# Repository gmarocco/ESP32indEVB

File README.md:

# ESP32indEVB
ESP32-S3 industrial development board

This board is based on ESP32-S3 chip and microcontoller
 - There are the following physical communication interfaces
   
 a) debug USB (it is connected to a UARTport of ESP32-S3)  
 
 b) native USB 
 
 c) isolated CANBUS with termination resistor 
 
 d) isolated RS485 with termination resistor 
 
 - There is a 9 RGB LED matrix (WS2812B) 
 
- There are 9 ESD protected GPIOs 

 - There is a free section of testpoints for experiment 

This is the third version of the board. With respect to the second version, some nets have been renamed and stiching vias along the board perimeter have been added

  You can open and modify the project with KiCad 9 release 
  For questions, feedback or proposals you can contact me at the following email: info@pcbsemplice.com
  
 !!! It is not allowed to reproduce the board for mass production and for business purposes. If you have a business proposal you can write at the following email: info@pcbsemplice.com
 
  Are you interested in these projects and want to contribute to the development of boards and projects (including open-source), prototypes, and documentation? You can make a no-obligation donation at this PayPal link: https://shorturl.at/0LquK Every contribution, no matter how small, makes a difference. Thank you!

Scheda di sviluppo industriale ESP32-S3  
Questa scheda è basata sul chip e microcontrollore ESP32-S3 

- Sono presenti le seguenti interfacce di comunicazione fisica:
  
a) USB di debug (collegata a una porta UART dell'ESP32-S3)  

b) USB nativa 

c) CANBUS isolato con resistenza di terminazione 

d) RS485 isolata con resistenza di terminazione 

- È presente una matrice di 9 LED RGB (WS2812B)

- Sono presenti 9 GPIO con protezione ESD  

- È disponibile una sezione gratuita di testpoint per esperimenti  
È possibile aprire e modificare il progetto con KiCad versione 9  

Questa è la terza verione della scheda. Rispetto alla seconda versione sono state rinominate alcune net e sono stati aggiunti dei fori di via stiching lungo il perimetro della scheda

Per domande feedback e suggerimenti mi puoi contattare al seguente indirizzo email: info@pcbsemplice.com

!!! E' vietato riprodurre la scheda per scopi commerciali. Per proposte commerciali puoi scrivere a info@pcbsemplice.com

Se parli Italiano e stai inziando con KiCad ti segnalo il percorso KiCadSemplice (www.pcbsemplice.com/kicad)
Se sei interessato a progettare circuiti professionali , è disponibile un percorso personalizzato chiamato pcb-pro-accademy 
  -  
  -  
  -  

Ti interessano questi progetti e vuoi contribuire per lo sviluppo di schede e progetti (anche open-source), prototipi, documentazione ? Puoi effettuare una donazione senza impegno a questo link di Paypal https://shorturl.at/0LquK Ogni contributo, anche piccolo, fa la differenza. Grazie!

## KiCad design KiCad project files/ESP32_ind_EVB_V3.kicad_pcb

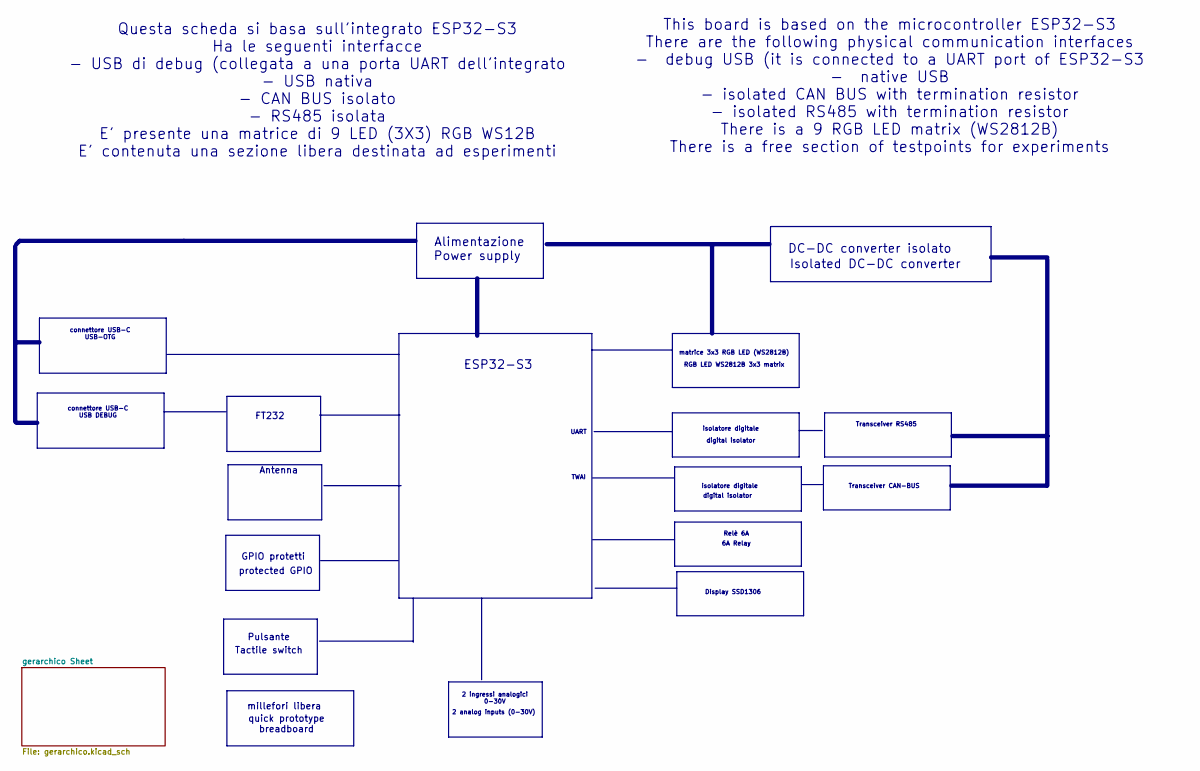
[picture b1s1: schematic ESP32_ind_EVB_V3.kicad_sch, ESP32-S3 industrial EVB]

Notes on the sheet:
TWAI
FT232
isolatore digitale
Transceiver RS485
matrice 3x3 RGB LED (WS2812B)
This board is based on the microcontroller ESP32-S3 There are the following physical communication interfaces - debug USB (it is connected to a UART port of ESP32-S3 - native USB - isolated CAN BUS with termination resistor - isolated RS485 with termination resistor There is a 9 RGB LED matrix (WS2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
Alimentazione
GPIO protetti
ESP32-S3
Transceiver CAN-BUS
millefori libera
Power supply
quick prototype breadboard
Questa scheda si basa sull'integrato ESP32-S3 Ha le seguenti interfacce - USB di debug (collegata a una porta UART dell'integrato - USB nativa - CAN BUS isolato - RS485 isolata E' presente una matrice di 9 LED (3X3) RGB WS12B E' contenuta una sezione libera destinata ad esperimenti
6A Relay
digital isolator
Pulsante
connettore USB-C USB-OTG
DC-DC converter isolato
Display SSD1306
Isolated DC-DC converter
2 analog inputs (0-30V)
protected GPIO
RGB LED WS2812B 3x3 matrix
Antenna
Relè 6A
2 ingressi analogici 0-30V
connettore USB-C USB DEBUG
Tactile switch
UART

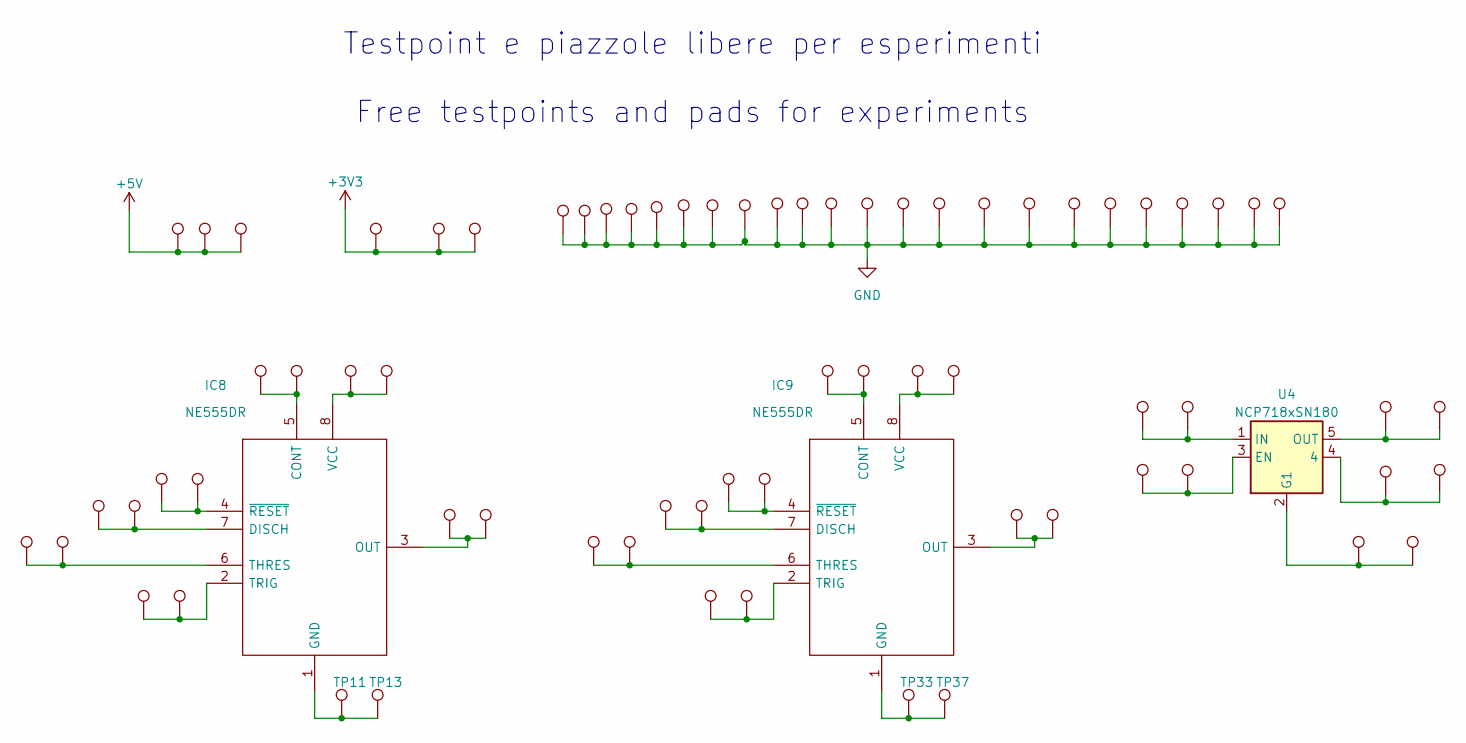
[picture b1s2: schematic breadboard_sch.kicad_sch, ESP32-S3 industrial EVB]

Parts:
IC8: NE555DR; SO-8_3.9x4.9mm_P1.27mm; Manufacturer_Part_Number NE555DR; Mouser Part Number 595-NE555DR
IC9: NE555DR; MSOP-8_3x3mm_P0.65mm; Manufacturer_Part_Number NE555DR; Mouser Part Number 595-NE555DR
TP1, TP2, TP3, TP4, TP5, TP6, TP7, TP8, TP9, TP10, TP11, TP12, TP13, TP14, TP15, TP16, TP17, TP18, TP19, TP20, TP21, TP22, TP23, TP24, TP25, TP26, TP27, TP28, TP29, TP30, TP31, TP32, TP33, TP34, TP35, TP36, TP37, TP38, TP39, TP40, TP41, TP42, TP43, TP44, TP45, TP46, TP47, TP48, TP49, TP50, TP51, TP52, TP53, TP54, TP55, TP56, TP57, TP58, TP59, TP60, TP61, TP62, TP63, TP64, TP65, TP66, TP67, TP68, TP69, TP70, TP71: TestPoint; TestPoint_Pad_through hole 1.5mm
U4: NCP718xSN180; SOT-23-5

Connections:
+3V3: TP25.1, TP29.1, TP30.1; also elsewhere on the board
+5V: TP17.1, TP18.1, TP19.1; also elsewhere on the board
GND: TP34.1, TP36.1, TP38.1, TP40.1, TP41.1, TP43.1, TP45.1, TP46.1, TP47.1, TP50.1, TP51.1, TP54.1, TP55.1, TP56.1, TP57.1, TP59.1, TP63.1, TP66.1, TP67.1, TP68.1, TP69.1, TP70.1, TP71.1; also elsewhere on the board
unnamed: IC8.5 (CONT), TP9.1, TP10.1
unnamed: IC8.7 (DISCH), TP3.1, TP4.1
unnamed: IC8.1 (GND), TP11.1, TP13.1
unnamed: IC8.3 (OUT), TP15.1, TP16.1
unnamed: IC8.6 (THRES), TP1.1, TP2.1
unnamed: IC8.2 (TRIG), TP5.1, TP7.1
unnamed: IC8.8 (VCC), TP12.1, TP14.1
unnamed: IC8.4 (~RESET), TP6.1, TP8.1
unnamed: IC9.5 (CONT), TP31.1, TP32.1
unnamed: IC9.7 (DISCH), TP22.1, TP23.1
unnamed: IC9.1 (GND), TP33.1, TP37.1
unnamed: IC9.3 (OUT), TP42.1, TP44.1
unnamed: IC9.6 (THRES), TP20.1, TP21.1
unnamed: IC9.2 (TRIG), TP24.1, TP27.1
unnamed: IC9.8 (VCC), TP35.1, TP39.1
unnamed: IC9.4 (~RESET), TP26.1, TP28.1
unnamed: TP61.1, TP65.1, U4.4
unnamed: TP49.1, TP53.1, U4.3 (EN)
unnamed: TP58.1, TP62.1, U4.2 (G1)
unnamed: TP48.1, TP52.1, U4.1 (IN)
unnamed: TP60.1, TP64.1, U4.5 (OUT)

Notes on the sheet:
Testpoint e piazzole libere per esperimenti Free testpoints and pads for experiments

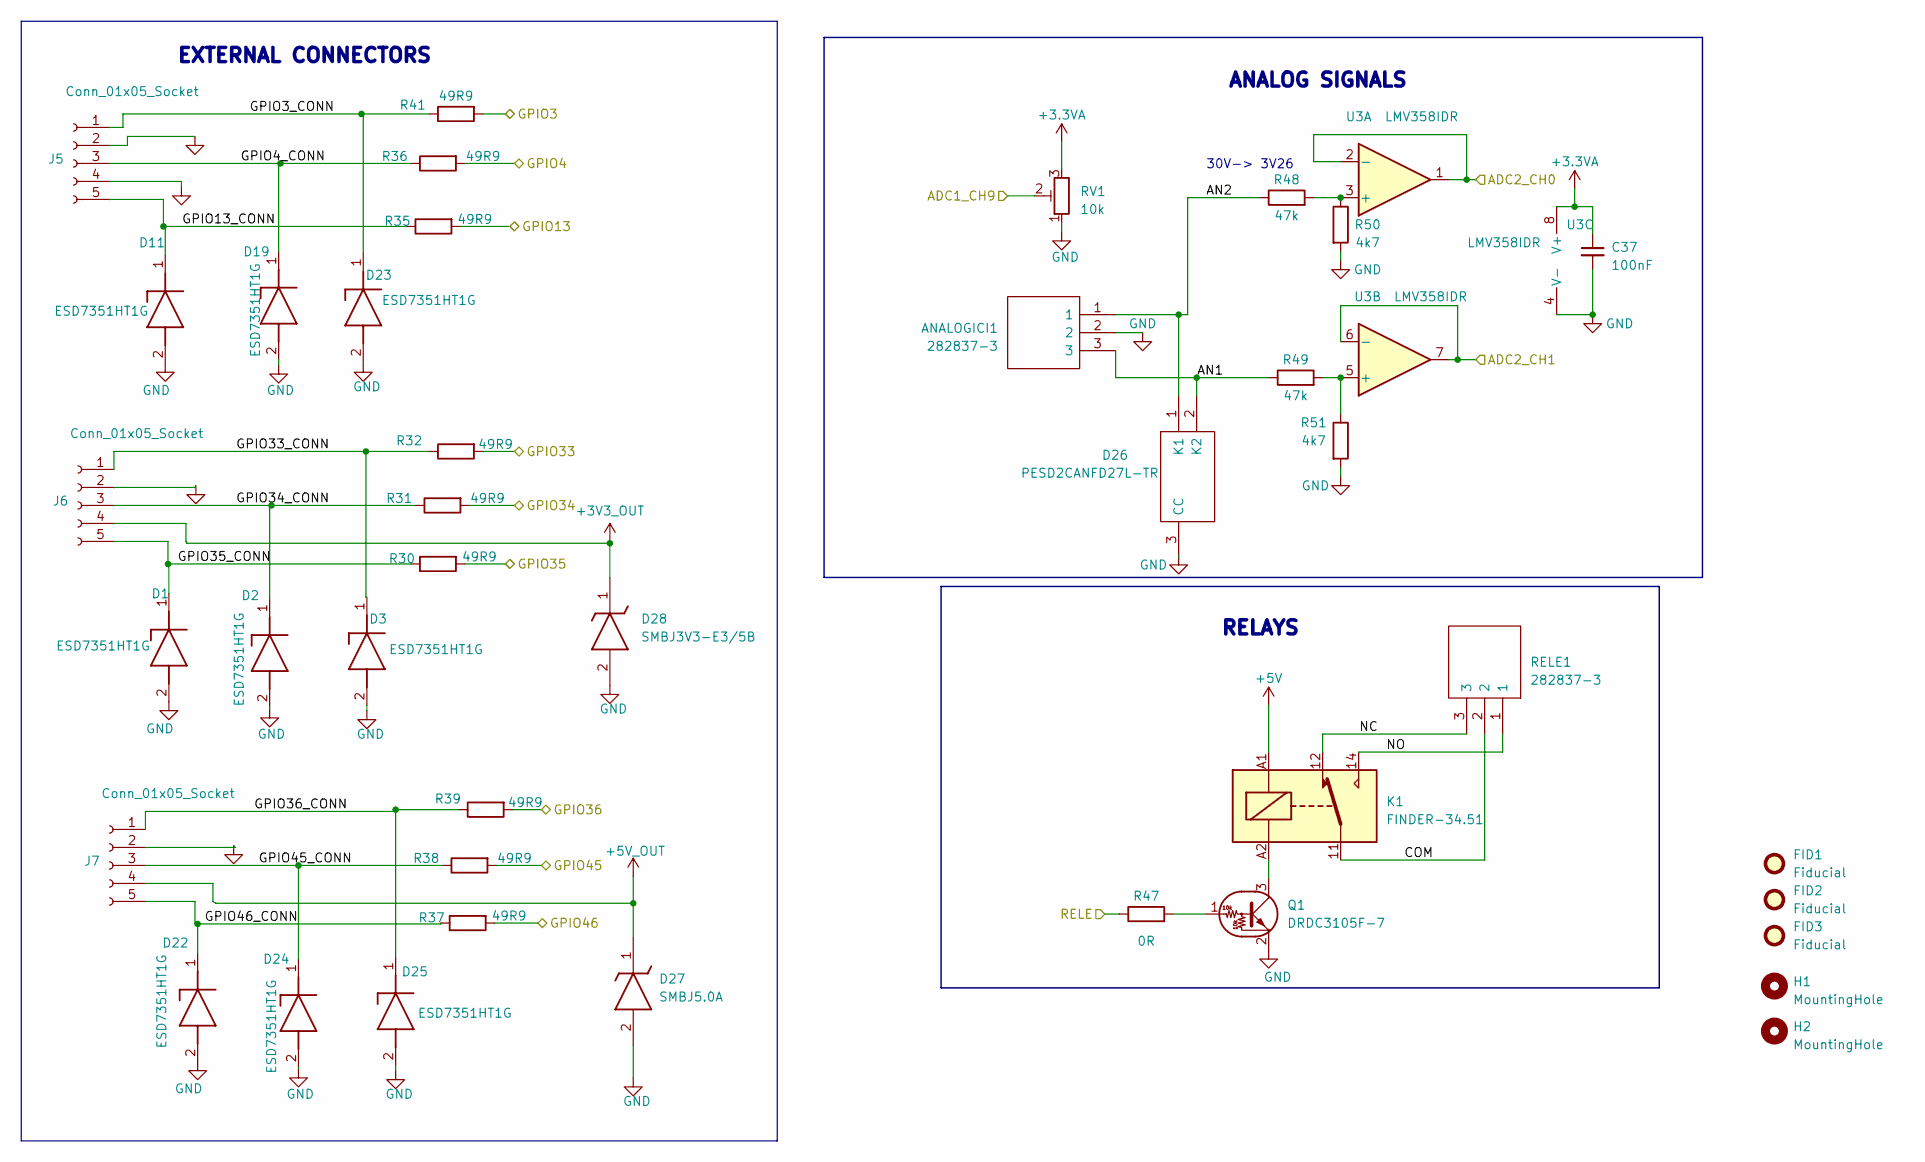
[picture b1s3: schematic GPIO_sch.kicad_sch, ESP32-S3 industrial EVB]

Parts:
ANALOGICI1: 282837-3; TerminalBlock_bornier-3_P5.08mm; Mouser Part Number 490-TB006-508-03BE
C37: 100nF; C_0603_1608Metric_Pad1.08x0.95mm_HandSolder
D1, D2, D3, D11, D19, D22, D23, D24, D25: ESD7351HT1G; SOD-323; Mouser Part Number 771-PESD3V3U1UB-T/R
D26: PESD2CANFD27L-TR; SOT-23-3; Mouser Part Number 771-PESD2CANFD24L-UX
D27: SMBJ5.0A; DIOM5436X244N; Mouser Part Number 78-SMBJ5.0A
D28: SMBJ3V3-E3/5B; DIOM5436X244N; Mouser Part Number 78-SMBJ5.0A
FID1, FID2, FID3: Fiducial; Fiducial_1.5mm_Mask3mm
H1, H2: MountingHole; MountingHole_3.2mm_M3
J5, J6, J7: Conn_01x05_Socket; PinSocket_1x05_P2.54mm_Vertical
K1: FINDER-34.51; Relay_SPDT_Finder_34.51_Vertical
Q1: DRDC3105F-7; SOT-23-3
R30, R31, R32, R35, R36, R37, R38, R39, R41: 49R9; R_0805_2012Metric_Pad1.20x1.40mm_HandSolder
R47: 0R; R_0603_1608Metric_Pad0.98x0.95mm_HandSolder
R48, R49: 47k; R_0603_1608Metric_Pad0.98x0.95mm_HandSolder
R50, R51: 4k7; R_0603_1608Metric_Pad0.98x0.95mm_HandSolder
RELE1: 282837-3; TerminalBlock_bornier-3_P5.08mm; Mouser Part Number 490-TB006-508-03BE
RV1: 10k; Potentiometer_Bourns_3314G_Vertical
U3: LMV358IDR; SO-8_3.9x4.9mm_P1.27mm

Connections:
+3.3VA: C37.1, RV1.3, U3.8 (V+); also elsewhere on the board
+3V3_OUT: D28.1 (K), J6.4; also elsewhere on the board
+5V: K1.A1; also elsewhere on the board
+5V_OUT: D27.1 (K), J7.4; also elsewhere on the board
/gerarchico Sheet/ESP32-S3 MCU/ADC1_CH9: RV1.2; also elsewhere on the board
/gerarchico Sheet/ESP32-S3 MCU/ADC2_CH0: U3.1, U3.2 (-); also elsewhere on the board
/gerarchico Sheet/ESP32-S3 MCU/ADC2_CH1: U3.6 (-), U3.7; also elsewhere on the board
/gerarchico Sheet/ESP32-S3 MCU/GPIO3: R41.2; also elsewhere on the board
/gerarchico Sheet/ESP32-S3 MCU/GPIO4: R36.2; also elsewhere on the board
/gerarchico Sheet/ESP32-S3 MCU/GPIO13: R35.2; also elsewhere on the board
/gerarchico Sheet/ESP32-S3 MCU/GPIO33: R32.2; also elsewhere on the board
/gerarchico Sheet/ESP32-S3 MCU/GPIO34: R31.2; also elsewhere on the board
/gerarchico Sheet/ESP32-S3 MCU/GPIO35: R30.2; also elsewhere on the board
/gerarchico Sheet/ESP32-S3 MCU/GPIO36: R39.2; also elsewhere on the board
/gerarchico Sheet/ESP32-S3 MCU/GPIO45: R38.2; also elsewhere on the board
/gerarchico Sheet/ESP32-S3 MCU/GPIO46: R37.2; also elsewhere on the board
/gerarchico Sheet/ESP32-S3 MCU/RELE: R47.1; also elsewhere on the board
/gerarchico Sheet/GPIO/AN1: ANALOGICI1.3, D26.2 (K2), R49.1
/gerarchico Sheet/GPIO/AN2: ANALOGICI1.1, D26.1 (K1), R48.1
/gerarchico Sheet/GPIO/COM: K1.11, RELE1.2
/gerarchico Sheet/GPIO/GPIO3_CONN: D23.1 (K), J5.1, R41.1
/gerarchico Sheet/GPIO/GPIO4_CONN: D19.1 (K), J5.3, R36.1
/gerarchico Sheet/GPIO/GPIO13_CONN: D11.1 (K), J5.5, R35.1
/gerarchico Sheet/GPIO/GPIO33_CONN: D3.1 (K), J6.1, R32.1
/gerarchico Sheet/GPIO/GPIO34_CONN: D2.1 (K), J6.3, R31.1
/gerarchico Sheet/GPIO/GPIO35_CONN: D1.1 (K), J6.5, R30.1
/gerarchico Sheet/GPIO/GPIO36_CONN: D25.1 (K), J7.1, R39.1
/gerarchico Sheet/GPIO/GPIO45_CONN: D24.1 (K), J7.3, R38.1
/gerarchico Sheet/GPIO/GPIO46_CONN: D22.1 (K), J7.5, R37.1
/gerarchico Sheet/GPIO/NC: K1.12, RELE1.3
/gerarchico Sheet/GPIO/NO: K1.14, RELE1.1
GND: ANALOGICI1.2, C37.2, D1.2 (A), D2.2 (A), D3.2 (A), D11.2 (A), D19.2 (A), D22.2 (A), D23.2 (A), D24.2 (A), D25.2 (A), D26.3 (CC), D27.2 (A), D28.2 (A), J5.2, J5.4, J6.2, J7.2, Q1.2 (E), R50.2, R51.2, RV1.1, U3.4 (V-); also elsewhere on the board
unnamed: Q1.1 (B), R47.2
unnamed: K1.A2, Q1.3 (C)
unnamed: R48.2, R50.1, U3.3 (+)
unnamed: R49.2, R51.1, U3.5 (+)

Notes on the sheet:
30V-> 3V26
ANALOG SIGNALS
RELAYS
EXTERNAL CONNECTORS

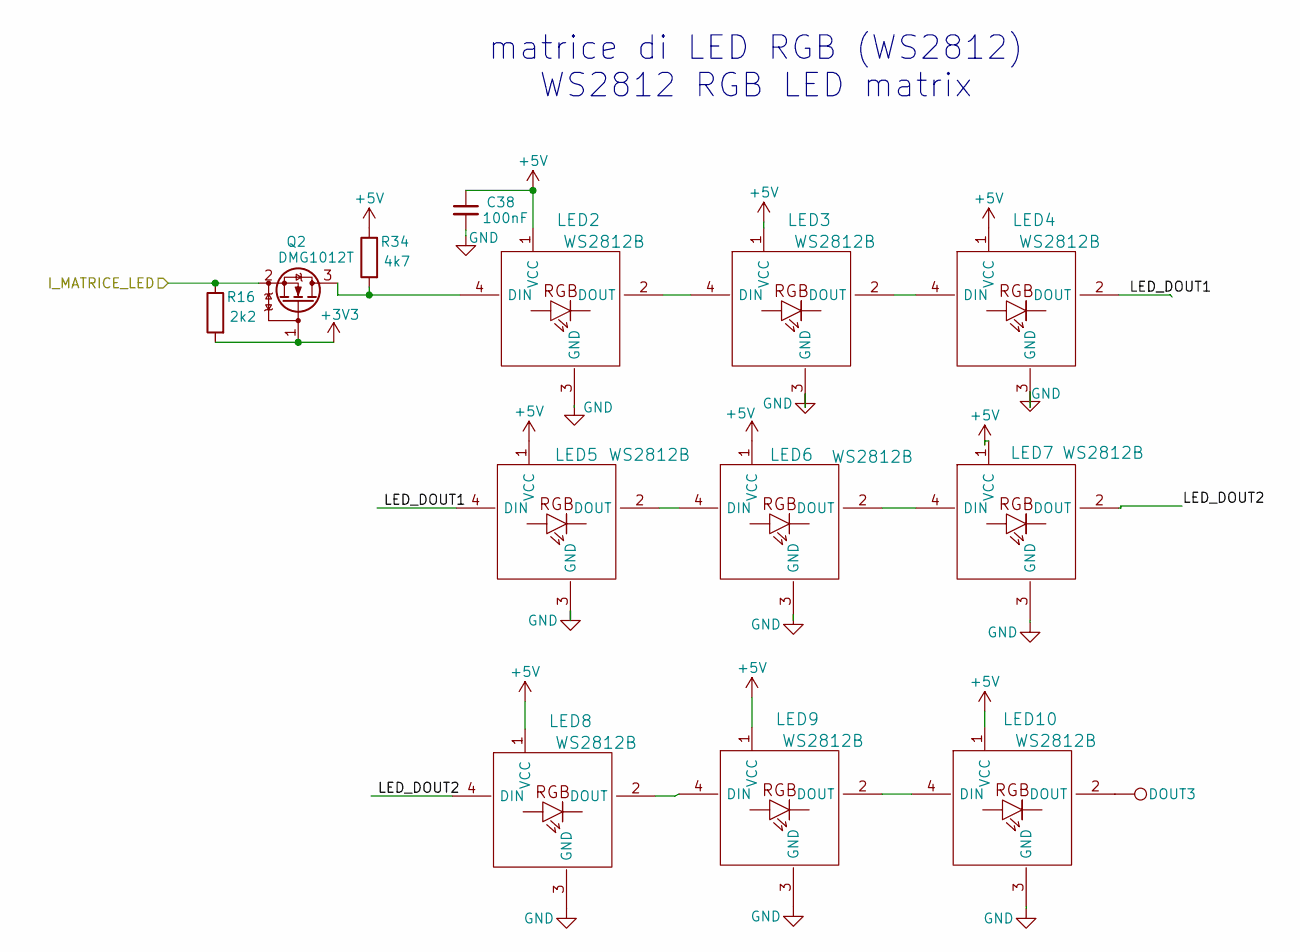
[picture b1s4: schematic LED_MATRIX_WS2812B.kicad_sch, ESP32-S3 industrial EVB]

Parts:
C38: 100nF; C_0603_1608Metric_Pad1.08x0.95mm_HandSolder
DOUT3: TestPoint; TestPoint_THTPad_D1.0mm_Drill0.5mm
LED2, LED3, LED4, LED5, LED6, LED7, LED8, LED9, LED10: WS2812B
Q2: DMG1012T; SOT-523
R16: 2k2; R_0603_1608Metric_Pad0.98x0.95mm_HandSolder
R34: 4k7; R_0603_1608Metric_Pad0.98x0.95mm_HandSolder

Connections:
+3V3: Q2.1 (G), R16.2; also elsewhere on the board
+5V: C38.1, LED2.1 (VCC), LED3.1 (VCC), LED4.1 (VCC), LED5.1 (VCC), LED6.1 (VCC), LED7.1 (VCC), LED8.1 (VCC), LED9.1 (VCC), LED10.1 (VCC), R34.1; also elsewhere on the board
/gerarchico Sheet/ESP32-S3 MCU/I_MATRICE_LED: Q2.2 (S), R16.1; also elsewhere on the board
/gerarchico Sheet/LED_MATRIX_WS2812B/LED_DOUT1: LED4.2 (DOUT), LED5.4 (DIN)
/gerarchico Sheet/LED_MATRIX_WS2812B/LED_DOUT2: LED7.2 (DOUT), LED8.4 (DIN)
GND: C38.2, LED2.3 (GND), LED3.3 (GND), LED4.3 (GND), LED5.3 (GND), LED6.3 (GND), LED7.3 (GND), LED8.3 (GND), LED9.3 (GND), LED10.3 (GND); also elsewhere on the board
unnamed: LED2.4 (DIN), Q2.3 (D), R34.2
unnamed: LED2.2 (DOUT), LED3.4 (DIN)
unnamed: LED3.2 (DOUT), LED4.4 (DIN)
unnamed: LED5.2 (DOUT), LED6.4 (DIN)
unnamed: LED6.2 (DOUT), LED7.4 (DIN)
unnamed: LED8.2 (DOUT), LED9.4 (DIN)
unnamed: LED9.2 (DOUT), LED10.4 (DIN)
unnamed: DOUT3.1, LED10.2 (DOUT)

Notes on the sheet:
matrice di LED RGB (WS2812) WS2812 RGB LED matrix

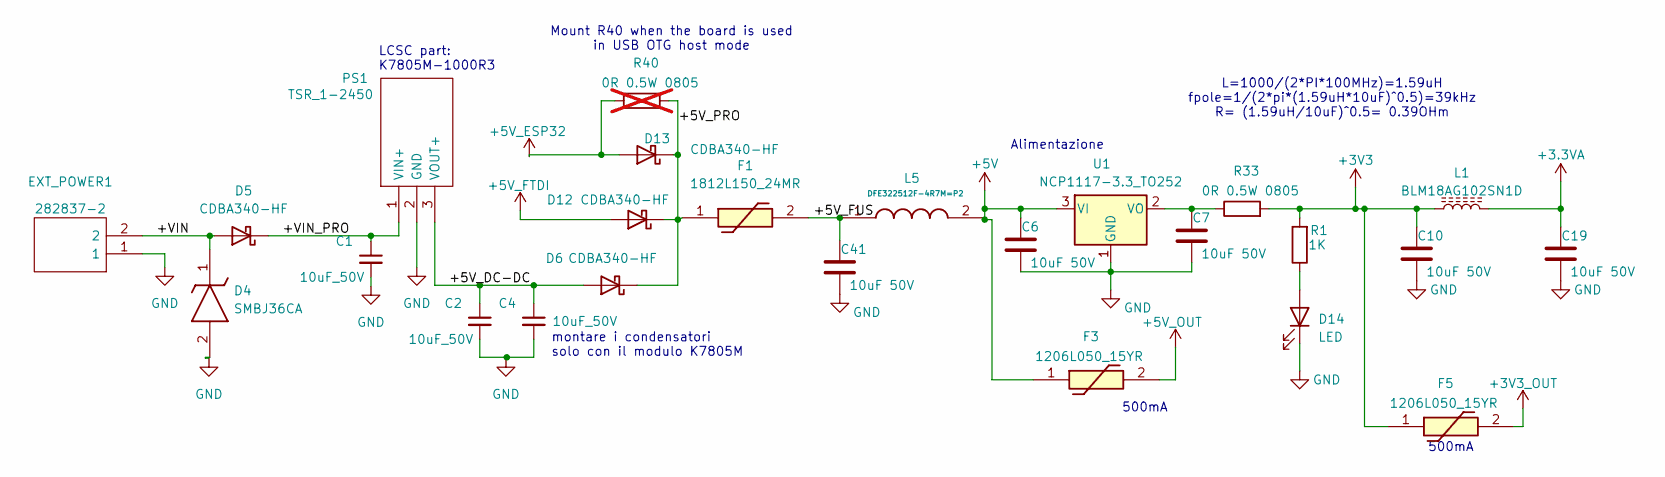
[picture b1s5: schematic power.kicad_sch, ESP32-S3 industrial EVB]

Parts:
C1, C2, C4: 10uF_50V; C_1206_3216Metric_Pad1.33x1.80mm_HandSolder
C6, C7, C10, C19, C41: 10uF 50V; C_1206_3216Metric_Pad1.33x1.80mm_HandSolder
D4: SMBJ36CA; DIOM5436X261N; Mouser Part Number SMBJ36CA
D5, D6, D12, D13: CDBA340-HF; SMA
D14: LED; LED_0603_1608Metric_Pad1.05x0.95mm_HandSolder
EXT_POWER1: 282837-2; 2828372; Mouser Part Number 571-2828372
F1: 1812L150_24MR; 1812L010DR; Mouser Part Number 576-1812L150/24MR
F3, F5: 1206L050_15YR; 1206L05015YR; Mouser Part Number 576-1206L050/15YR
L1: BLM18AG102SN1D; L_0603_1608Metric_Pad1.05x0.95mm_HandSolder
L5: DFE322512F-4R7M=P2; 1277ASH100MP2; Mouser Part Number 81-DFE322512F-4R7MP2
PS1: TSR_1-2450; Converter_DCDC_TRACO_TSR-1_THT; Mouser Part Number 495-TSR-1-2450
R1: 1K; R_0603_1608Metric_Pad0.98x0.95mm_HandSolder
R33: 0R 0.5W 0805; R_0805_2012Metric_Pad1.20x1.40mm_HandSolder
R40: 0R 0.5W 0805; R_0805_2012Metric_Pad1.20x1.40mm_HandSolder; not fitted
U1: NCP1117-3.3_TO252; TO-252-2

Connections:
+3.3VA: C19.1, L1.2; also elsewhere on the board
+3V3: C10.1, F5.1, L1.1, R1.2, R33.2; also elsewhere on the board
+3V3_OUT: F5.2; also elsewhere on the board
+5V: C6.1, F3.1, L5.2, U1.3 (VI); also elsewhere on the board
+5V_ESP32: D13.2 (A), R40.1; also elsewhere on the board
+5V_FTDI: D12.2 (A); also elsewhere on the board
+5V_OUT: F3.2; also elsewhere on the board
/gerarchico Sheet/Power/+5V_DC-DC: C2.1, C4.1, D6.2 (A), PS1.3 (VOUT+)
/gerarchico Sheet/Power/+5V_FUS: C41.1, F1.2, L5.1
/gerarchico Sheet/Power/+5V_PRO: D6.1 (K), D12.1 (K), D13.1 (K), F1.1, R40.2
/gerarchico Sheet/Power/+VIN: D4.1 (K), D5.2 (A), EXT_POWER1.2
/gerarchico Sheet/Power/+VIN_PRO: C1.1, D5.1 (K), PS1.1 (VIN+)
GND: C1.2, C2.2, C4.2, C6.2, C7.2, C10.2, C19.2, C41.2, D4.2 (A), D14.1 (K), EXT_POWER1.1, PS1.2 (GND), U1.1 (GND); also elsewhere on the board
unnamed: D14.2 (A), R1.1
unnamed: C7.1, R33.1, U1.2 (VO)

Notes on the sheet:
500mA
L=1000/(2*PI*100MHz)=1.59uH fpole=1/(2*pi*(1.59uH*10uF)^0.5)=39kHz R= (1.59uH/10uF)^0.5= 0.39OHm
LCSC part: K7805M-1000R3
Mount R40 when the board is used in USB OTG host mode
montare i condensatori solo con il modulo K7805M
Alimentazione

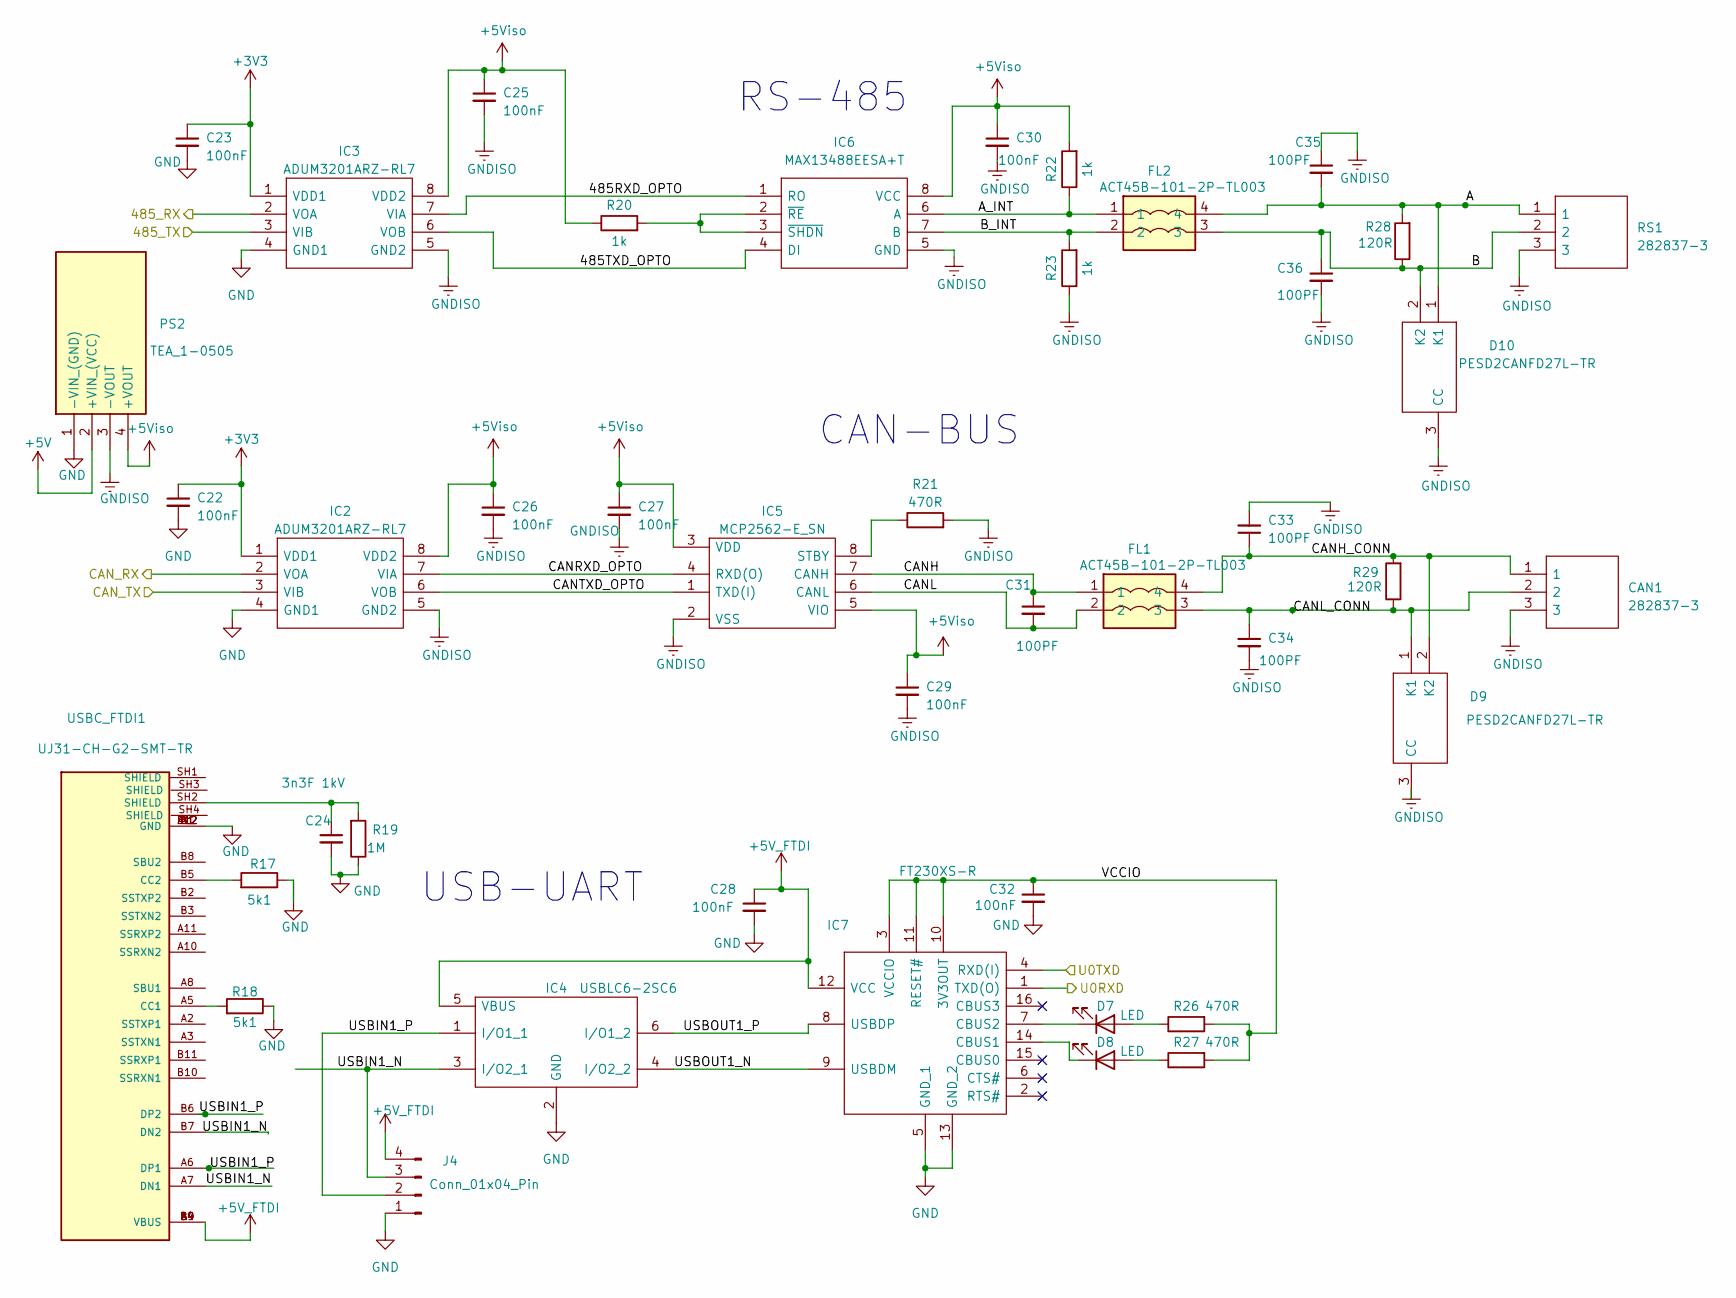
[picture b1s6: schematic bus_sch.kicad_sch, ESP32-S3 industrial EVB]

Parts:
C22, C23, C25, C26, C27, C28, C29, C30, C32: 100nF; C_0603_1608Metric_Pad1.08x0.95mm_HandSolder
C24: 3n3F 1kV; C_1206_3216Metric_Pad1.33x1.80mm_HandSolder
C31, C33, C34, C35, C36: 100PF; C_0603_1608Metric_Pad1.08x0.95mm_HandSolder
CAN1: 282837-3; TerminalBlock_bornier-3_P5.08mm; Mouser Part Number 490-TB006-508-03BE
D7, D8: LED; LED_0603_1608Metric_Pad1.05x0.95mm_HandSolder
D9, D10: PESD2CANFD27L-TR; SOT-23-3; Mouser Part Number 771-PESD2CANFD24L-UX
FL1, FL2: ACT45B-101-2P-TL003; ACT45B1012PTL003; Mouser Part Number 810-ACT1210D1012PTL0
IC2, IC3: ADUM3201ARZ-RL7; SO-8_3.9x4.9mm_P1.27mm; Mouser Part Number 584-ADUM3201ARZ-R7
IC4: USBLC6-2SC6; SOT23-6; Mouser Part Number 511-USBLC6-2SC6
IC5: MCP2562-E_SN; SO-8_3.9x4.9mm_P1.27mm; Mouser Part Number 579-MCP2562-E/SN
IC6: MAX13488EESA+T; SO-8_3.9x4.9mm_P1.27mm; Mouser Part Number 700-MAX13488EESAT
IC7: FT230XS-R; TSSOP-16_4.4x5mm_P0.65mm; Mouser Part Number 895-FT230XS-R
J4: Conn_01x04_Pin; PinHeader_1x04_P2.54mm_Vertical
PS2: TEA_1-0505; TEA10505; Mouser Part Number 495-TEA1-0505
R17, R18: 5k1; R_0603_1608Metric_Pad0.98x0.95mm_HandSolder
R19: 1M; R_0603_1608Metric_Pad0.98x0.95mm_HandSolder
R20, R22, R23: 1k; R_0603_1608Metric_Pad0.98x0.95mm_HandSolder
R21, R26, R27: 470R; R_0603_1608Metric_Pad0.98x0.95mm_HandSolder
R28, R29: 120R; R_0805_2012Metric_Pad1.20x1.40mm_HandSolder
RS1: 282837-3; TerminalBlock_bornier-3_P5.08mm; Mouser Part Number 490-TB006-508-03BE
USBC_FTDI1: UJ31-CH-G2-SMT-TR; UJ31CHG2SMTTR; PART_REV 1.01

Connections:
+3V3: C22.1, C23.1, IC2.1 (VDD1), IC3.1 (VDD1); also elsewhere on the board
+5V: PS2.2 (+VIN_(VCC)); also elsewhere on the board
+5V_FTDI: C28.1, IC4.5 (VBUS), IC7.12 (VCC), J4.4, USBC_FTDI1.A4 (VBUS), USBC_FTDI1.A9 (VBUS), USBC_FTDI1.B4 (VBUS), USBC_FTDI1.B9 (VBUS); also elsewhere on the board
+5Viso: C25.1, C26.1, C27.1, C29.1, C30.1, IC2.8 (VDD2), IC3.8 (VDD2), IC5.3 (VDD), IC5.5 (VIO), IC6.8 (VCC), PS2.4 (+VOUT), R20.1, R22.2
/gerarchico Sheet/ESP32-S3 MCU/485_RX: IC3.2 (VOA); also elsewhere on the board
/gerarchico Sheet/ESP32-S3 MCU/485_TX: IC3.3 (VIB); also elsewhere on the board
/gerarchico Sheet/ESP32-S3 MCU/CAN_RX: IC2.2 (VOA); also elsewhere on the board
/gerarchico Sheet/ESP32-S3 MCU/CAN_TX: IC2.3 (VIB); also elsewhere on the board
/gerarchico Sheet/ESP32-S3 MCU/U0RXD: IC7.1 (TXD(O)); also elsewhere on the board
/gerarchico Sheet/ESP32-S3 MCU/U0TXD: IC7.4 (RXD(I)); also elsewhere on the board
/gerarchico Sheet/bus/485RXD_OPTO: IC3.7 (VIA), IC6.1 (RO)
/gerarchico Sheet/bus/485TXD_OPTO: IC3.6 (VOB), IC6.4 (DI)
/gerarchico Sheet/bus/A: C35.2, D10.1 (K1), FL2.4, R28.2, RS1.1
/gerarchico Sheet/bus/A_INT: FL2.1, IC6.6 (A), R22.1
/gerarchico Sheet/bus/B: C36.1, D10.2 (K2), FL2.3, R28.1, RS1.2
/gerarchico Sheet/bus/B_INT: FL2.2, IC6.7 (B), R23.2
/gerarchico Sheet/bus/CANH: C31.1, FL1.1, IC5.7 (CANH)
/gerarchico Sheet/bus/CANH_CONN: C33.1, CAN1.1, D9.2 (K2), FL1.4, R29.2
/gerarchico Sheet/bus/CANL: C31.2, FL1.2, IC5.6 (CANL)
/gerarchico Sheet/bus/CANL_CONN: C34.1, CAN1.2, D9.1 (K1), FL1.3, R29.1
/gerarchico Sheet/bus/CANRXD_OPTO: IC2.7 (VIA), IC5.4 (RXD(O))
/gerarchico Sheet/bus/CANTXD_OPTO: IC2.6 (VOB), IC5.1 (TXD(I))
/gerarchico Sheet/bus/USBIN1_N: IC4.3 (I/O2_1), J4.3, USBC_FTDI1.A7 (DN1), USBC_FTDI1.B7 (DN2)
/gerarchico Sheet/bus/USBIN1_P: IC4.1 (I/O1_1), J4.2, USBC_FTDI1.A6 (DP1), USBC_FTDI1.B6 (DP2)
/gerarchico Sheet/bus/USBOUT1_N: IC4.4 (I/O2_2), IC7.9 (USBDM)
/gerarchico Sheet/bus/USBOUT1_P: IC4.6 (I/O1_2), IC7.8 (USBDP)
/gerarchico Sheet/bus/VCCIO: C32.1, IC7.3 (VCCIO), IC7.10 (3V3OUT), IC7.11 (RESET#), R26.2, R27.2
GND: C22.2, C23.2, C24.2, C28.2, C32.2, IC2.4 (GND1), IC3.4 (GND1), IC4.2 (GND), IC7.5 (GND_1), IC7.13 (GND_2), J4.1, PS2.1 (-VIN_(GND)), R17.1, R18.1, R19.1, USBC_FTDI1.A1 (GND), USBC_FTDI1.A12 (GND), USBC_FTDI1.B1 (GND), USBC_FTDI1.B12 (GND); also elsewhere on the board
GNDISO: C25.2, C26.2, C27.2, C29.2, C30.2, C33.2, C34.2, C35.1, C36.2, CAN1.3, D9.3 (CC), D10.3 (CC), IC2.5 (GND2), IC3.5 (GND2), IC5.2 (VSS), IC6.5 (GND), PS2.3 (-VOUT), R21.2, R23.1, RS1.3
unnamed: C24.1, R19.2, USBC_FTDI1.SH2 (SHIELD)
unnamed: D7.2 (A), R26.1
unnamed: D7.1 (K), IC7.7 (CBUS2)
unnamed: D8.2 (A), R27.1
unnamed: D8.1 (K), IC7.14 (CBUS1)
unnamed: IC5.8 (STBY), R21.1
unnamed: IC6.2 (~RE), IC6.3 (~SHDN), R20.2
unnamed: R18.2, USBC_FTDI1.A5 (CC1)
unnamed: R17.2, USBC_FTDI1.B5 (CC2)

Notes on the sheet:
USB-UART
CAN-BUS
RS-485
